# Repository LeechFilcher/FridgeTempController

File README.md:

CHANGELOG:
==================================================
Additions:
- Added Wiring Diagrams
- Fixed Folder Structure to be a bit better

BEFORE YOU START:
==================================================
There are a few Requirements for this to work.
First off you need special a Temperature Controller for the whole project to work.
I'm currently using DHT22 AM2302 but any Digital Temperature sensor will work.
I'm using a NodeESP in this example but this is very overkill. The Cheapest and worst Arduino will do except you want to add some
smart functionality to this example.
You also need a little speaker. I'm using a higher quality speaker here I had lying around but depending on how far away the fridge is a simple piezo maybe enough.

Note that the Wiring diagram is provided AS IS and will probably not change much anymore. I may add this to a hub that I'm planning to work on to see if your fridge needs defrosting however (this is why this is using a humidity / temperature sensor too)

This is the wiring diagram and board design currently used for Prototyping:

LICENSE: 
==================================================
* Developed by Deamonic Networks / Lukas Duerr e.K.
<p xmlns:dct="http://purl.org/dc/terms/" xmlns:vcard="http://www.w3.org/2001/vcard-rdf/3.0#">
  
  <br />
  To the extent possible under law,
  <a rel="dct:publisher"
     href="https://creativecommons.org/share-your-work/public-domain/cc0/">
    <span property="dct:title">Lukas Duerr e.k.</span></a>
  has waived all copyright and related or neighboring rights to
  <span property="dct:title">FridgeTempController</span>.
This work is published from:
<span property="vcard:Country" datatype="dct:ISO3166"
      content="DE" about="https://creativecommons.org/share-your-work/public-domain/cc0/">
  Germany</span>.
</p>
 
 About Commits:
==================================================
Dailys (even though they do not occur daily) fix small bugs and usually took only a few minutes to develop. So more or less they fix stuff that wasn't really a issue or implement libary updates. They do **NOT** Feature Major changes or Bugfixes for anything noted. Daily updates are __**NOT**__ recommended in production usage, I recommend using a commit from the Release site.

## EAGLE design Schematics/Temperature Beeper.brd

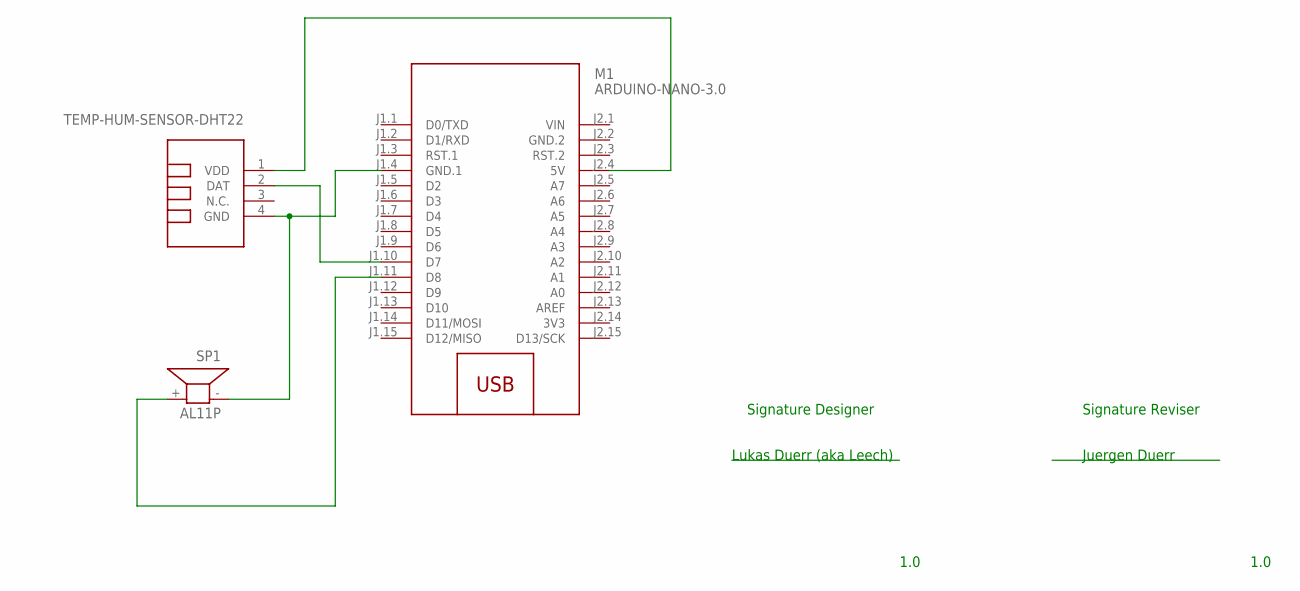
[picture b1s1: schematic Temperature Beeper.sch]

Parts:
M1: ARDUINO-NANO-3.0
SP1: AL11P
U$2: TEMP-HUM-SENSOR-DHT22

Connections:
3V3: M1.J2.14 (3V3)
GND.2: M1.J2.2 (GND.2)
unnamed: M1.J1.11 (D8), SP1.+ (2)
unnamed: M1.J1.4 (GND.1), SP1.- (1), U$2.4 (GND)
unnamed: M1.J2.4 (5V), U$2.1 (VDD)
unnamed: M1.J1.10 (D7), U$2.2 (DAT)
VIN: M1.J2.1 (VIN)

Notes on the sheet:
Signature Designer
Signature Reviser
1.0
Lukas Duerr (aka Leech)
Juergen Duerr

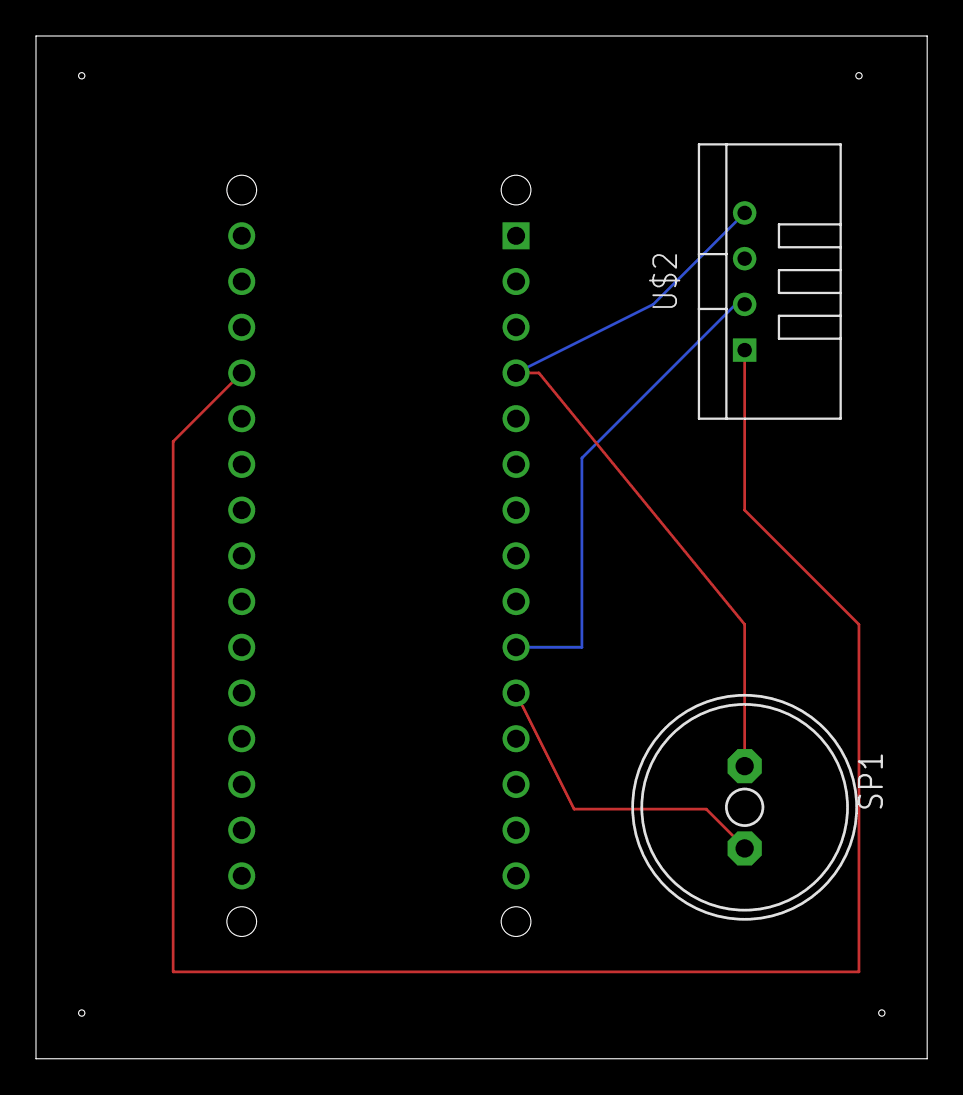
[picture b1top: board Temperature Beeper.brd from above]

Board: 2 copper layers, 49.5 x 56.8 mm, 3 parts (1 on the bottom side), 4 nets.

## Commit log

2020-02-26 Uploaded Source Code
    This is the first and probably only commit I will make. Since this is an Insanely simple software.
2020-02-29 Added Schematics
2020-02-29 Changed File Structure to my standards

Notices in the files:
parts and their libraries:
diy-modules: Released under the Creative Commons Attribution 4.0 International License: http://creativecommons.org/licenses/by/4.0
